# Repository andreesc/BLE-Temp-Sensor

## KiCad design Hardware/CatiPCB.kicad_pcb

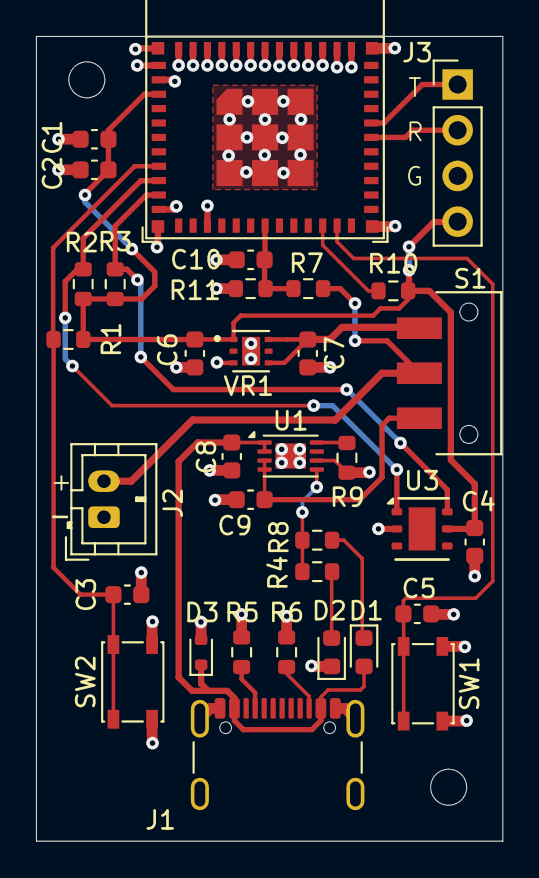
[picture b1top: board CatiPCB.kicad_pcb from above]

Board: 2 copper layers, 25.9 x 44.7 mm, 36 parts (0 on the bottom side), 20 nets.

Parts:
C1: 10uF; C_0603_1608Metric
C2, C4, C5, C10: 0.1uF; C_0603_1608Metric
C3, C6, C7: 1uF; C_0603_1608Metric
C8, C9: 4.7uF; C_0603_1608Metric
D1: RED; LED_0603_1608Metric
D2: GREEN; LED_0603_1608Metric
D3: TPD1E10B06DPYR; D_SOD-523
H1, H2: MountingHole; MountingHole_2mm
J1: USB_C_Receptacle_USB2.0_16P; USB_C_Receptacle_GCT_USB4105-xx-A_16P_TopMnt_Horizontal
J2: Bat_Conn; JST_PH_B2B-PH-K_1x02_P2.00mm_Vertical
J3: UART; PinHeader_1x04_P2.54mm_Vertical
R1, R10: 10KΩ; R_0603_1608Metric
R2, R3: 4.7KΩ; R_0603_1608Metric
R4, R8: 470Ω; R_0603_1608Metric
R5, R6: 5.1KΩ; R_0603_1608Metric
R7: 470KΩ; R_0603_1608Metric
R9: 2KΩ; R_0603_1608Metric
R11: 100KΩ; R_0603_1608Metric
S1: JS102011SAQN; SW_JS102011SAQN
SW1: BOOT; SW_SPST_PTS810
SW2: RESET; SW_SPST_PTS810
U1: MCP73831-2-MC; DFN-8-1EP_3x2mm_P0.5mm_EP1.7x1.4mm
U3: HDC1080; Texas_PWSON-N6
U5: ESP32-H2-MINI-1
VR1: TLV75533PDRVR; VREG_TLV75533PDRVR

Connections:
+3V3: C1.1, C2.1, C4.1, C6.1, J3.4, R1.1, R2.1, R3.1, R10.1, U3.5 (VCC), U5.3 (3V3), VR1.1 (OUT)
/EN: C3.1, R1.2, SW2.3 (K), SW2.4 (A), U5.8 (EN)
/GPIO4: C10.1, R7.2, R11.1, U5.18 (GPIO4/FSPICLK/ADC1_CH3/MTCK)
/GPIO9: C5.1, SW1.3 (K), SW1.4 (A), U5.23 (GPIO9)
/OUT: C7.1, S1.3, VR1.4 (EN), VR1.6 (IN)
/SCL: R3.2, U3.6 (SCL), U5.10 (GPIO1/FSPICS0/ADC1_CH0)
/SDA: R2.2, U3.1 (SDA), U5.9 (GPIO0/FSPIQ)
/U0RXD: J3.2, U5.30 (GPIO23/FSPICS1/U0RXD)
/U0TXD: J3.1, U5.31 (GPIO24/FSPICS2/U0TXD)
/USB_5V: C8.2, D1.2 (A), D3.1, J1.A4 (VBUS), J1.A9 (VBUS), J1.B4 (VBUS), J1.B9 (VBUS), U1.1 (V_{DD}), U1.2 (V_{DD})
/V_BAT: J2.2, R7.1, S1.2
GND: C1.2, C2.2, C3.2, C4.2, C5.2, C6.2, C7.2, C8.1, C9.2, C10.2, D2.1 (K), D3.2, J1.A1 (GND), J1.A12 (GND), J1.B1 (GND), J1.B12 (GND), J1.S1 (SHIELD), J2.1, J3.3, R5.2, R6.1, R9.2, R11.2, SW1.1, SW1.2, SW2.2, U1.6 (V_{SS}), U1.9, U3.2 (GND), U5.1 (GND), U5.2 (GND), U5.11 (GND), U5.14 (GND), U5.36 (GND), U5.37 (GND), U5.38 (GND), U5.39 (GND), U5.40 (GND), U5.41 (GND), U5.42 (GND), U5.43 (GND), U5.44 (GND), U5.45 (GND), U5.46 (GND), U5.47 (GND), U5.48 (GND), U5.49 (GND), U5.50 (GND), U5.51 (GND), U5.52 (GND), U5.53 (GND), VR1.3 (GND), VR1.7 (EXP)
unnamed: C9.1, S1.1, U1.3 (V_{BAT}), U1.4 (V_{BAT})
unnamed: D1.1 (K), R8.2
unnamed: D2.2 (A), R4.1
unnamed: J1.A5 (CC1), R5.1
unnamed: J1.B5 (CC2), R6.2
unnamed: R9.1, U1.8 (PROG)
unnamed: R4.2, R8.1, U1.5 (STAT)
unnamed: R10.2, U5.22 (GPIO8)

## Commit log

2024-11-28 README.md
2024-12-01 Adicionando firmware base
2024-12-01 Adding gitignore file
2024-12-01 Gitignore
2024-12-04 Refactoring read temp function
2024-12-10 Read battery level
2024-12-14 Implemented I2C reading
2024-12-16 Minor fix
2024-12-31 HDC1080 Component and BLE Fixes
2024-12-31 Removing build directories from tracking
2024-12-31 New gitignore
2025-01-03 Add voltage reading with BLE
2025-02-01 Add hardware files
